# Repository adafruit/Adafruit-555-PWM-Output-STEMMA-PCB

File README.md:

## Adafruit 555 PWM Output STEMMA - 1.4K to 25 KHz or 1.4 to 250 Hz - STEMMA JST PH 2mm PCB

<a href="http://www.adafruit.com/products/5963"><br/>
Click here to purchase one from the Adafruit shop</a>

PCB files for the Adafruit 555 PWM Output STEMMA - 1.4K~25 KHz or 1.4~250 Hz - STEMMA JST PH 2mm. 

Format is EagleCAD schematic and board layout
* https://www.adafruit.com/product/5963

### Description

How many times have we heard "hey you could have just replaced that microcontroller with a 555"? Maybe 555 times! But we always find wiring up a timer chip to be a bit of a pain, you need quite a few components - especially if you want a buffered output. That's why we designed the Adafruit 555 PWM Output STEMMA - a fully-assembled 555 timer board with adjustable PWM square-wave output.

We originally came up with this idea when someone requested we make a 'PC Fan Dummy' board, that can generate a 100Hz signal for faking a PC fan's tachometer signal to a motherboard. But then we thought that sometimes we want a square wave for driving a piezo, or as an audio input, or to modulate an IR signal. So we made it a little more general-purpose.

You can select between two 'ranges': approximately 1.4K~25 KHz or 1.4~250 Hz. The onboard trimmer pot will tune the actual output between those values. You can use a logic analyzer, oscilloscope, multimeter with frequency-counting, or even an audio input jack on a computer, to determine the precise value if you need more than a rough number. The output is a DC square wave, driven by a 74HC1G04
buffer so it can sink/source up to 12.5mA.

You can power the board from 3V to 12VDC, an onboard regulator will pin the input to the 555 and buffer to 5V max. That means that between 3V and 5V power, the signal peak will be at the same logic level as the power. Above 5V, the output will be pegged to 5V.

Each STEMMA board is a fully assembled and tested PCB but no cable. No soldering is required to use it, but you will need to pick up a 2mm pitch, 3-pin STEMMA JST PH cable. Alternatively, if you do want to solder, there's a 0.1" spaced header for power/ground/signal.

### License

Adafruit invests time and resources providing this open source design, please support Adafruit and open-source hardware by purchasing products from [Adafruit](https://www.adafruit.com)!

Designed by Limor Fried/Ladyada for Adafruit Industries.

Creative Commons Attribution/Share-Alike, all text above must be included in any redistribution. 
See license.txt for additional details.

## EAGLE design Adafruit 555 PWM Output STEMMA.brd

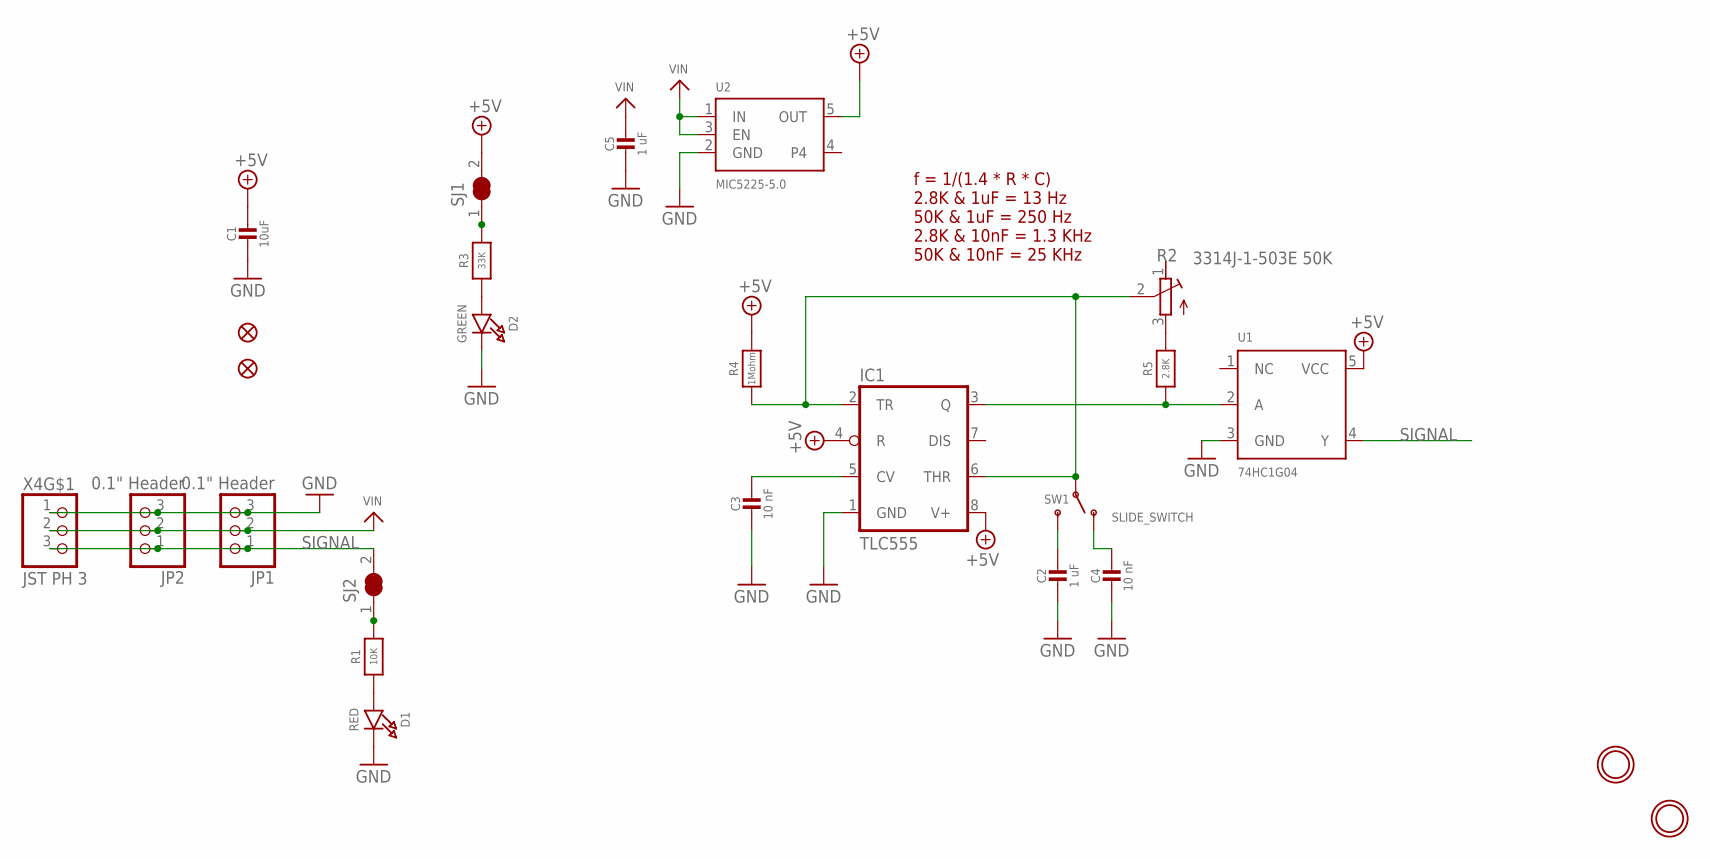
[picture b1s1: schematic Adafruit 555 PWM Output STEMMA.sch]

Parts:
C1: 10uF; 0805-NO
C2, C5: 1 uF; 0603-NO
C3, C4: 10 nF; 0603-NO
D1: RED; CHIPLED_0603_NOOUTLINE
D2: GREEN; CHIPLED_0603_NOOUTLINE
FID2, FID3: FIDUCIAL_1MM
IC1: TLC555; SO08
JP1: 0.1" Header; 1X03_OVAL
JP2: 0.1" Header; 1X03_ROUND
R1: 10K; 0603-NO
R2: 3314J-1-503E 50K; RTRIM3314J
R3: 33K; 0603-NO
R4: 1Mohm; 0603-NO
R5: 2.8K; 0603-NO
SJ1, SJ2: SOLDERJUMPER_CLOSED; SOLDERJUMPER_CLOSEDWIRE
SW1: SLIDE_SWITCH; SPDT_SMT_SSSS811101
U1: 74HC1G04; SC70-5
U2: MIC5225-5.0; SOT23-5
U$1, U$8: MOUNTINGHOLE2.5; MOUNTINGHOLE_2.5_PLATED
X4: JST PH 3; JSTPH3

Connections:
+5V: C1.1, IC1.4 (R), IC1.8 (V+), R4.2, SJ1.2, U1.5 (VCC), U2.5 (OUT)
GND: C1.2, C2.2, C3.2, C4.2, C5.2, D1.C, D2.C, IC1.1 (GND), JP1.3, JP2.3, U1.3 (GND), U2.2 (GND), X4.1
unnamed: R3.2, SJ1.1
unnamed: D1.A, R1.1
unnamed: R1.2, SJ2.1
unnamed: C2.1, SW1.C (S)
unnamed: IC1.2 (TR), IC1.6 (THR), R2.2 (S), R4.1, SW1.B
unnamed: C3.1, IC1.5 (CV)
unnamed: C4.1, SW1.A (O)
unnamed: R2.3 (A), R5.2
unnamed: IC1.3 (Q), R5.1, U1.2 (A)
unnamed: D2.A, R3.1
SIGNAL: JP1.1, JP2.1, SJ2.2, U1.4 (Y), X4.3
VIN: C5.1, JP1.2, JP2.2, U2.1 (IN), U2.3 (EN), X4.2

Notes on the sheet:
f = 1/(1.4 * R * C) 2.8K & 1uF = 13 Hz 50K & 1uF = 250 Hz 2.8K & 10nF = 1.3 KHz 50K & 10nF = 25 KHz

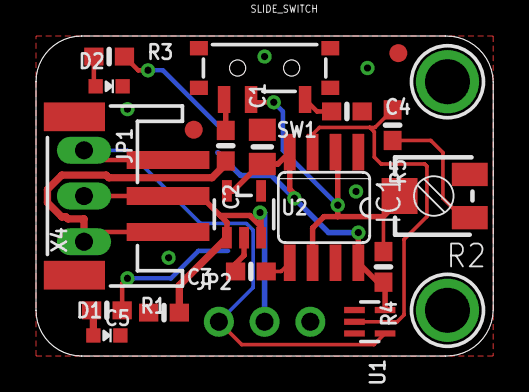
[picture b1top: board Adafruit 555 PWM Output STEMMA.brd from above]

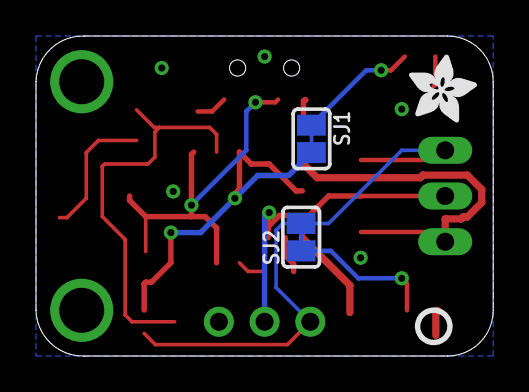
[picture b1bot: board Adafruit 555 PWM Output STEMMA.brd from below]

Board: 2 copper layers, 25.4 x 17.8 mm, 43 parts (11 on the bottom side), 14 nets.

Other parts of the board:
PLABEL0: PLABEL0
PLABEL1: PLABEL1
PLABEL7: PLABEL7
PLABEL8: PLABEL8
PLABEL9: PLABEL9
PLABEL13: PLABEL13
PLABEL14: PLABEL14
PLABEL15: PLABEL15
PLABEL19: PLABEL19
PLABEL20: PLABEL20
PLABEL21: PLABEL21
PLABEL22: PLABEL22
PLABEL23: PLABEL23
PLABEL24: PLABEL24
PLABEL25: PLABEL25
PLABEL26: PLABEL26
U$5: PCBFEAT-REV-040
U$15: ADAFRUIT_3.5MM

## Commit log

2024-05-10 cookiecutter

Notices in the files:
parts and their libraries:
microbuilder: This work is placed in the public domain, and may be freely used for commercial and non-commercial work with the following conditions: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
